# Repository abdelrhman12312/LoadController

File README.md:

# LoadController
you can view the circuit here :
https://kicanvas.org/?github=https%3A%2F%2Fgithub.com%2Fabdelrhman12312%2FLoadController%2Ftree%2Fmain%2FMotorControlV1.0

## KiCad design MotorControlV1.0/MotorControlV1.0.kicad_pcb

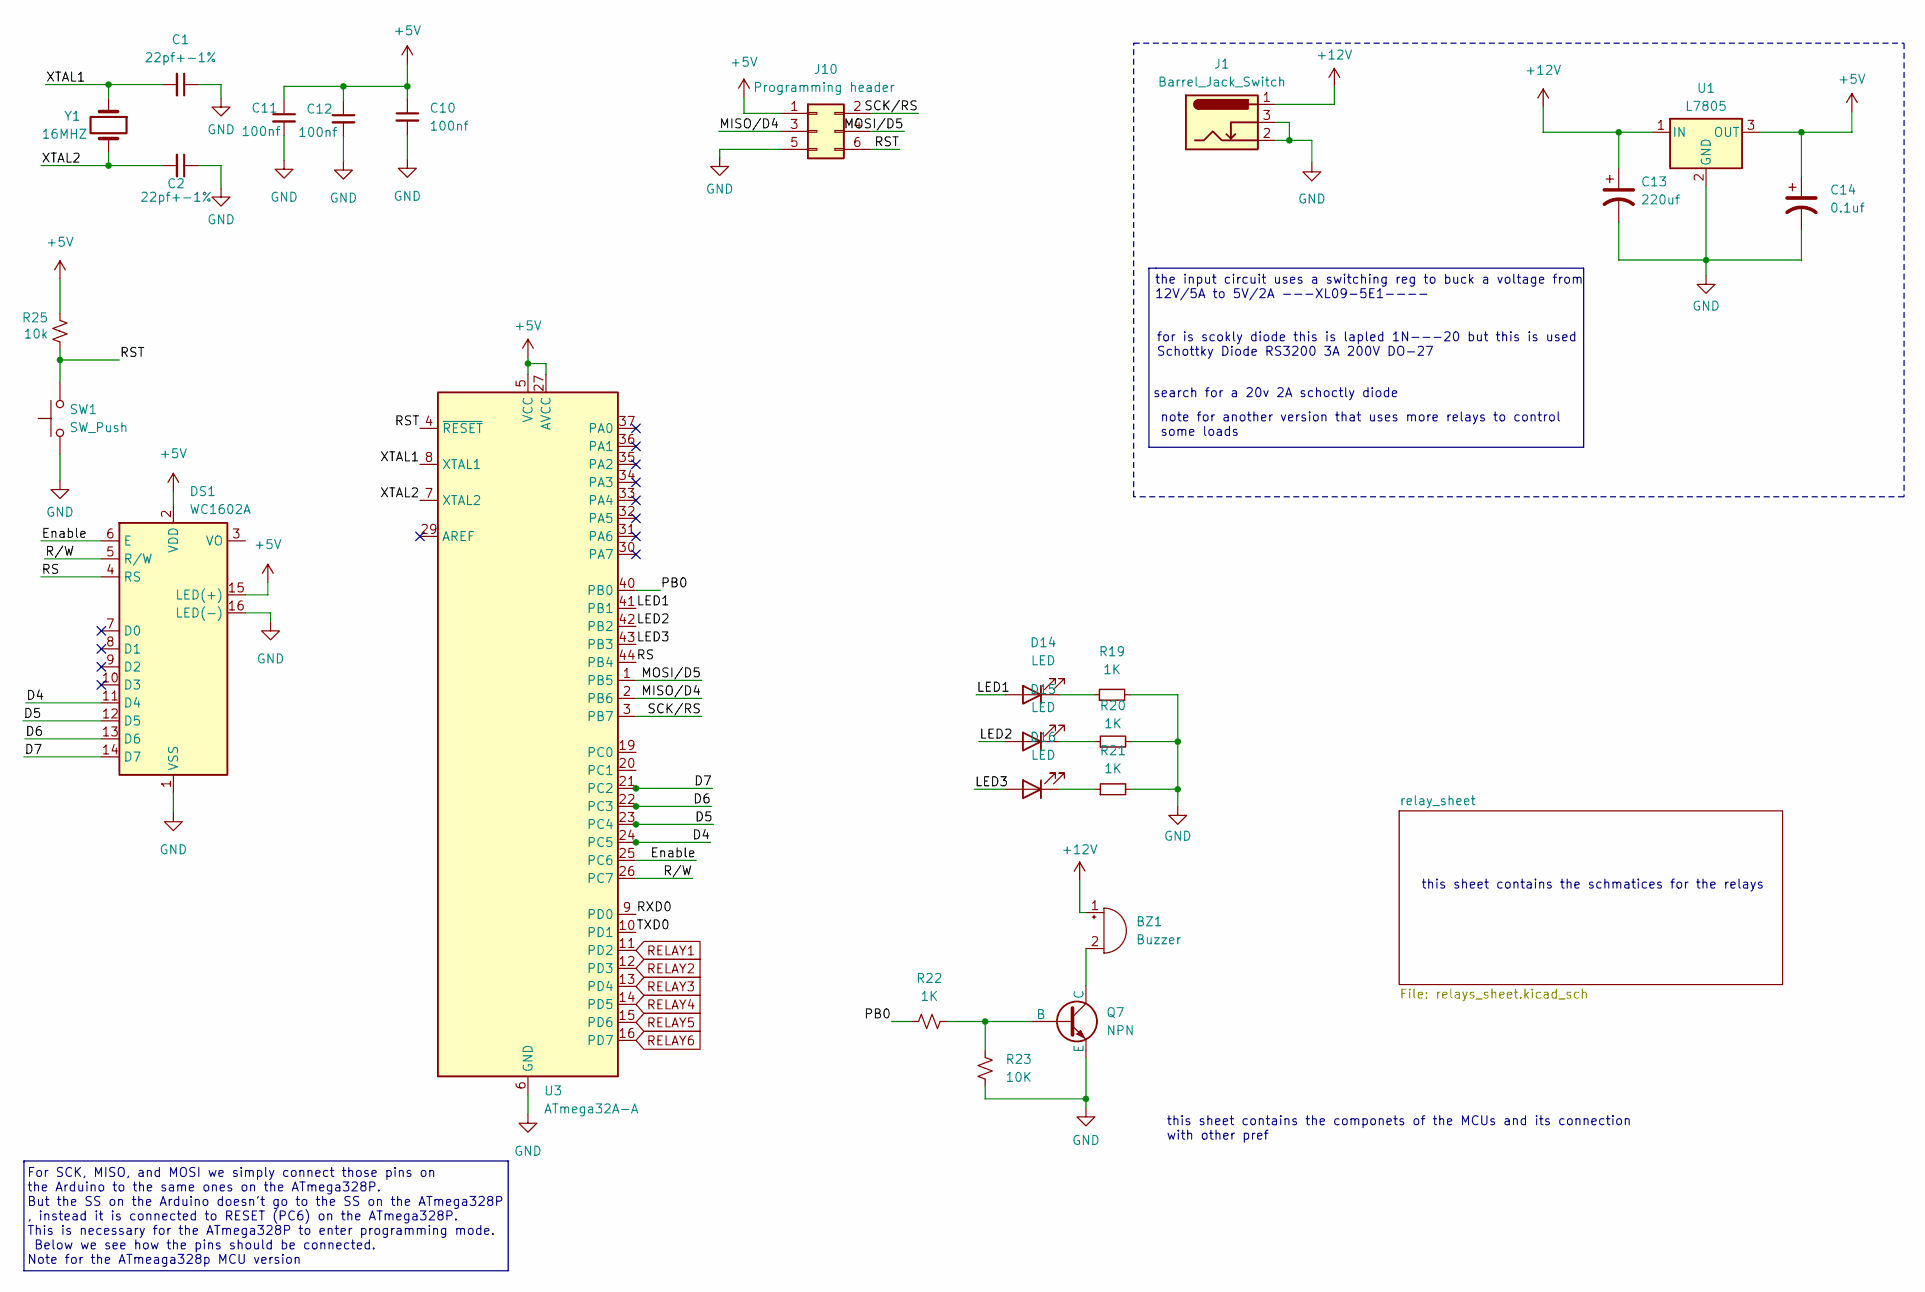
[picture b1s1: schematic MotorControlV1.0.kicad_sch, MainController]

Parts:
BZ1: Buzzer; Buzzer_12x9.5RM7.6
C1, C2: 22pf+-1%; C_0805_2012Metric_Pad1.18x1.45mm_HandSolder
C10, C11, C12: 100nf; C_0402_1005Metric_Pad0.74x0.62mm_HandSolder
C13: 220uf; CP_Radial_D8.0mm_P2.50mm
C14: 0.1uf; CP_Radial_D8.0mm_P2.50mm
D14, D15, D16: LED; LED_1206_3216Metric_Pad1.42x1.75mm_HandSolder
DS1: WC1602A
J1: Barrel_Jack_Switch; BarrelJack_Horizontal
J10: Programming header; PinHeader_1x06_P2.54mm_Vertical
Q7: NPN; SOT-23
R19, R20, R21, R22: 1K; R_1206_3216Metric_Pad1.30x1.75mm_HandSolder
R23: 10K; R_1206_3216Metric_Pad1.30x1.75mm_HandSolder
R25: 10k; R_1206_3216Metric_Pad1.30x1.75mm_HandSolder
SW1: SW_Push; SW_Push_SPST_NO_Alps_SKRK
U1: L7805; TO-220-3_Horizontal_TabDown
U3: ATmega32A-A; TQFP-44_10x10mm_P0.8mm
Y1: 16MHZ; Crystal_HC49-U_Vertical

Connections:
+5V: C10.1, C11.1, C12.1, C14.1, DS1.2 (VDD), DS1.15 (LED(+)), J10.1, R25.2, U1.3 (OUT), U3.5 (VCC), U3.17 (VCC), U3.27 (AVCC), U3.38 (VCC)
+12V: BZ1.1 (-), C13.1, J1.1, U1.1 (IN); also elsewhere on the board
/D4: DS1.11 (D4), U3.24 (PC5)
/D5: DS1.12 (D5), U3.23 (PC4)
/D6: DS1.13 (D6), U3.22 (PC3)
/D7: DS1.14 (D7), U3.21 (PC2)
/Enable: DS1.6 (E), U3.25 (PC6)
/LED1: D14.2 (A), U3.41 (PB1)
/LED2: D15.2 (A), U3.42 (PB2)
/LED3: D16.2 (A), U3.43 (PB3)
/MISO/D4: J10.3, U3.2 (PB6)
/MOSI/D5: J10.4, U3.1 (PB5)
/PB0: R22.1, U3.40 (PB0)
/RS: DS1.4 (RS), U3.44 (PB4)
/RST: J10.6, R25.1, SW1.2, U3.4 (~RESET)
/RXD0: U3.9 (PD0)
/R/W: DS1.5 (R/W), U3.26 (PC7)
/SCK/RS: J10.2, U3.3 (PB7)
/TXD0: U3.10 (PD1)
/XTAL1: C1.2, U3.8 (XTAL1), Y1.1
/XTAL2: C2.2, U3.7 (XTAL2), Y1.2
GND: C1.1, C2.1, C10.2, C11.2, C12.2, C13.2, C14.2, DS1.1 (VSS), DS1.16 (LED(-)), J1.2, J1.3, J10.5, Q7.3 (E), R19.2, R20.2, R21.2, R23.2, SW1.1, U1.2 (GND), U3.6 (GND), U3.18 (GND), U3.28 (GND), U3.39 (GND); also elsewhere on the board
unnamed: BZ1.2 (+), Q7.1 (C)
unnamed: D14.1 (K), R19.1
unnamed: D15.1 (K), R20.1
unnamed: D16.1 (K), R21.1
unnamed: Q7.2 (B), R22.2, R23.1
RELAY1: U3.11 (PD2); also elsewhere on the board
RELAY2: U3.12 (PD3); also elsewhere on the board
RELAY3: U3.13 (PD4); also elsewhere on the board
RELAY4: U3.14 (PD5); also elsewhere on the board
RELAY5: U3.15 (PD6); also elsewhere on the board
RELAY6: U3.16 (PD7); also elsewhere on the board

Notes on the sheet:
this sheet contains the schmatices for the relays
For SCK, MISO, and MOSI we simply connect those pins on the Arduino to the same ones on the ATmega328P. But the SS on the Arduino doesn't go to the SS on the ATmega328P , instead it is connected to RESET (PC6) on the ATmega328P. This is necessary for the ATmega328P to enter programming mode. Below 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
note for another version that uses more relays to control some loads
for is scokly diode this is lapled 1N---20 but this is used Schottky Diode RS3200 3A 200V DO-27
the input circuit uses a switching reg to buck a voltage from 12V/5A to 5V/2A ---XL09-5E1----
search for a 20v 2A schoctly diode
this sheet contains the componets of the MCUs and its connection with other pref

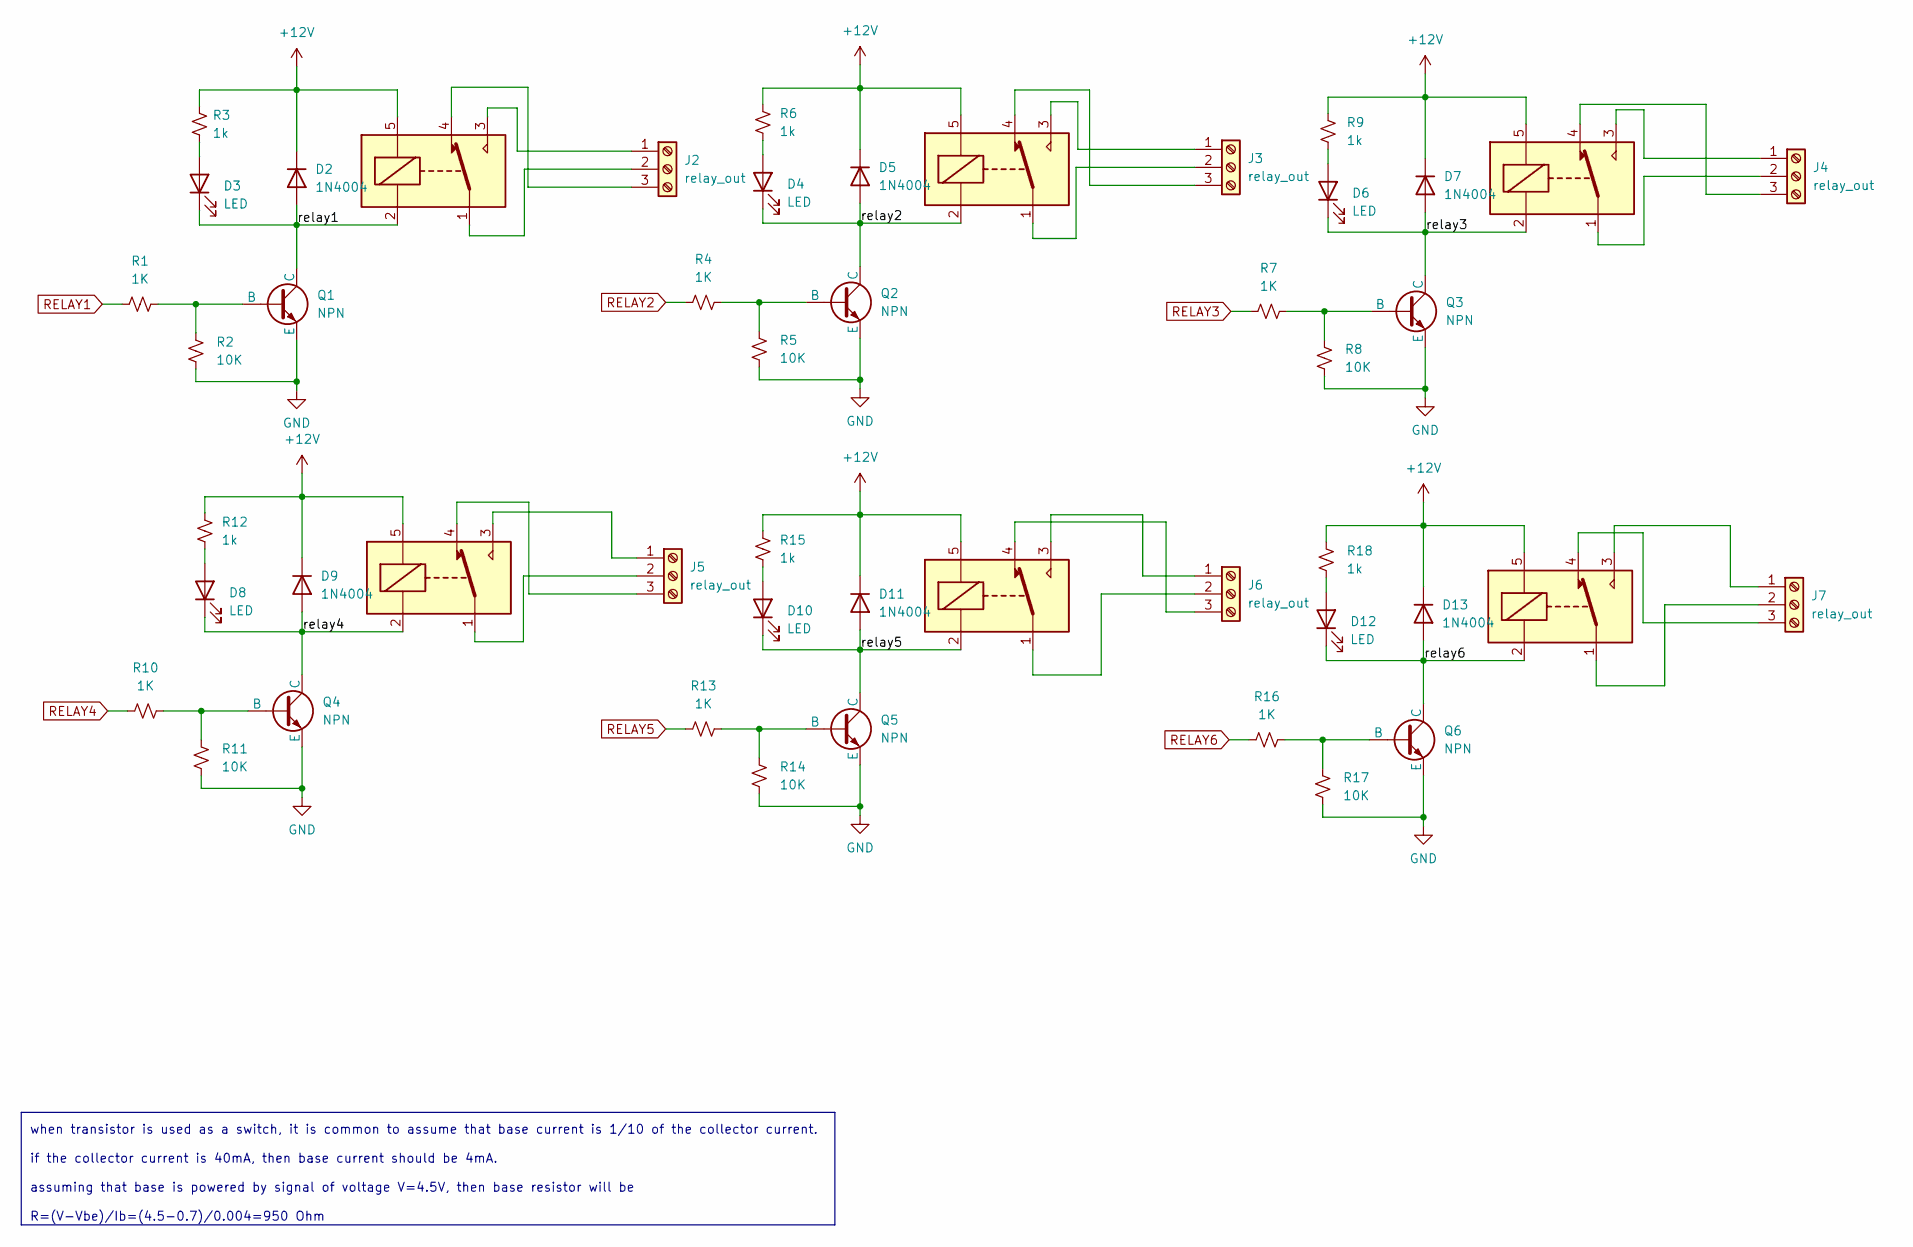
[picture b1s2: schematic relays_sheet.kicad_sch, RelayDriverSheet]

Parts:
D2, D5, D7, D9, D11, D13: 1N4004; D_SMA_Handsoldering
D3, D4, D6, D8, D10, D12: LED; LED_1206_3216Metric_Pad1.42x1.75mm_HandSolder
J2, J3, J4, J5, J6, J7: relay_out; TerminalBlock_Phoenix_MKDS-1,5-3_1x03_P5.00mm_Horizontal
K1, K2, K3, K4, K5, K6: G5LE-1; Relay_SPDT_Omron-G5LE-1
Q1, Q2, Q3, Q4, Q5, Q6: NPN; SOT-23
R1, R4, R7, R10, R13, R16: 1K; R_1206_3216Metric_Pad1.30x1.75mm_HandSolder
R2, R5, R8, R11, R14, R17: 10K; R_1206_3216Metric_Pad1.30x1.75mm_HandSolder
R3, R6, R9, R12, R15, R18: 1k; R_1206_3216Metric_Pad1.30x1.75mm_HandSolder

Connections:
+12V: D2.1 (K), D5.1 (K), D7.1 (K), D9.1 (K), D11.1 (K), D13.1 (K), K1.5, K2.5, K3.5, K4.5, K5.5, K6.5, R3.1, R6.1, R9.1, R12.1, R15.1, R18.1; also elsewhere on the board
/relay_sheet/relay1: D2.2 (A), D3.1 (K), K1.2, Q1.1 (C)
/relay_sheet/relay2: D4.1 (K), D5.2 (A), K2.2, Q2.1 (C)
/relay_sheet/relay3: D6.1 (K), D7.2 (A), K3.2, Q3.1 (C)
/relay_sheet/relay4: D8.1 (K), D9.2 (A), K4.2, Q4.1 (C)
/relay_sheet/relay5: D10.1 (K), D11.2 (A), K5.2, Q5.1 (C)
/relay_sheet/relay6: D12.1 (K), D13.2 (A), K6.2, Q6.1 (C)
GND: Q1.3 (E), Q2.3 (E), Q3.3 (E), Q4.3 (E), Q5.3 (E), Q6.3 (E), R2.2, R5.2, R8.2, R11.2, R14.2, R17.2; also elsewhere on the board
unnamed: D3.2 (A), R3.2
unnamed: D4.2 (A), R6.2
unnamed: D6.2 (A), R9.2
unnamed: D8.2 (A), R12.2
unnamed: D10.2 (A), R15.2
unnamed: D12.2 (A), R18.2
unnamed: J2.1, K1.3
unnamed: J2.2, K1.1
unnamed: J2.3, K1.4
unnamed: J3.1, K2.3
unnamed: J3.2, K2.1
unnamed: J3.3, K2.4
unnamed: J4.1, K3.3
unnamed: J4.2, K3.1
unnamed: J4.3, K3.4
unnamed: J5.1, K4.3
unnamed: J5.2, K4.1
unnamed: J5.3, K4.4
unnamed: J6.1, K5.3
unnamed: J6.2, K5.1
unnamed: J6.3, K5.4
unnamed: J7.1, K6.3
unnamed: J7.2, K6.1
unnamed: J7.3, K6.4
unnamed: Q1.2 (B), R1.2, R2.1
unnamed: Q2.2 (B), R4.2, R5.1
unnamed: Q3.2 (B), R7.2, R8.1
unnamed: Q4.2 (B), R10.2, R11.1
unnamed: Q5.2 (B), R13.2, R14.1
unnamed: Q6.2 (B), R16.2, R17.1
RELAY1: R1.1; also elsewhere on the board
RELAY2: R4.1; also elsewhere on the board
RELAY3: R7.1; also elsewhere on the board
RELAY4: R10.1; also elsewhere on the board
RELAY5: R13.1; also elsewhere on the board
RELAY6: R16.1; also elsewhere on the board

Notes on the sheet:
when transistor is used as a switch, it is common to assume that base current is 1/10 of the collector current. if the collector current is 40mA, then base current should be 4mA. assuming that base is powered by signal of voltage V=4.5V, then base resistor will be R=(V-Vbe)/Ib=(4.5-0.7)/0.004=950 O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

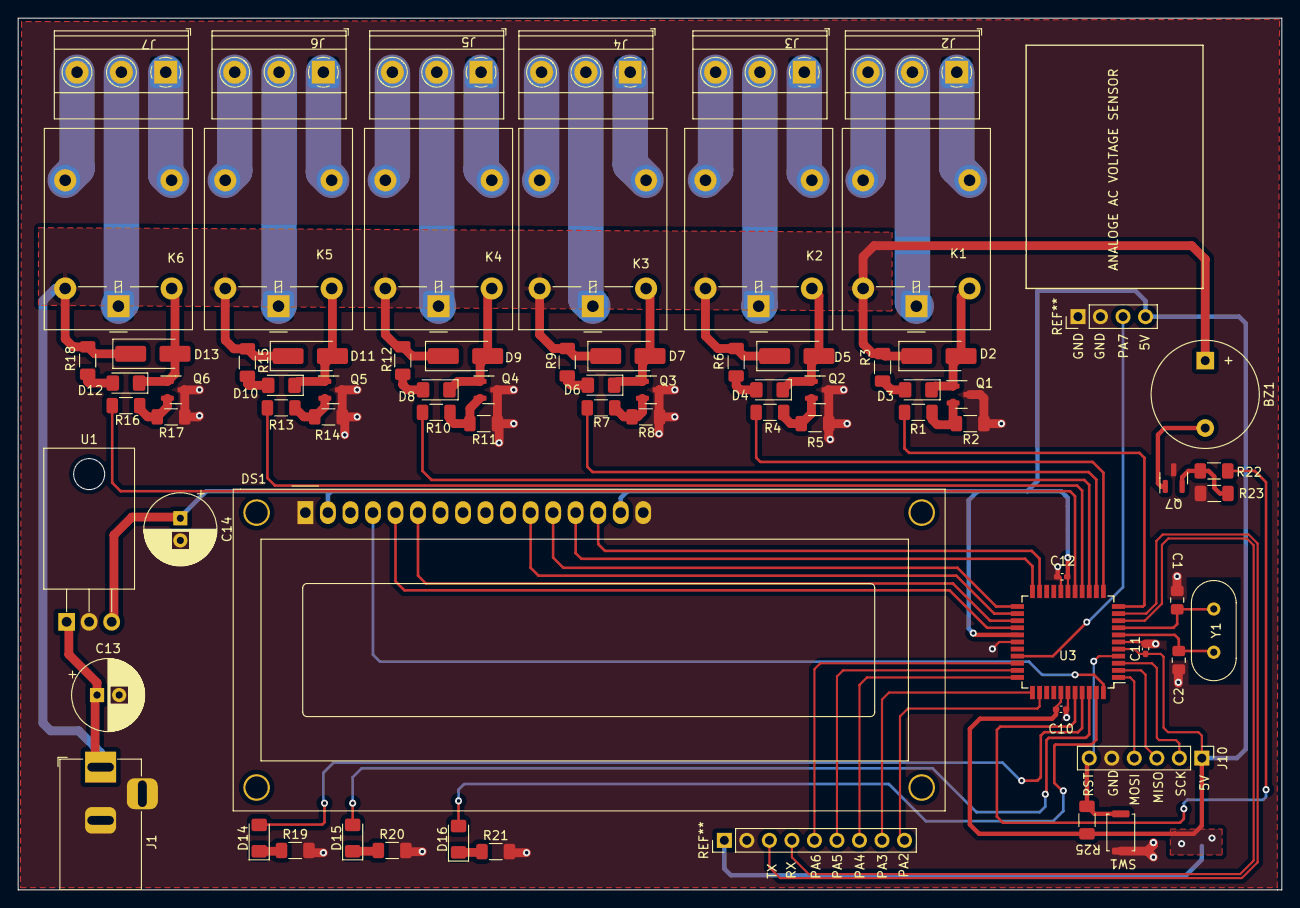
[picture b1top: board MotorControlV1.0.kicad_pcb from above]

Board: 2 copper layers, 142.5 x 98.3 mm, 73 parts (0 on the bottom side), 67 nets.
